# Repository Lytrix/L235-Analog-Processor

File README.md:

# L-235 Analog Processor ##

### Introduction ###
I was interested in the [SR-235](https://www.thinksrs.com/images/instr/boxcar/SR235_FPlg.jpg) as being the equivalent mathematical processor but then in Analog form which I saw in action on Hainbach's channel using this test equipment here: https://www.youtube.com/watch?v=PS_cn9-rgEs 
Also coming from a digital synthesis world using a Kurzweil K2000R Synthesizer years ago which has an awesome VAST engine with mathematical functions called FUN to combine 2 signals and apply mathematical functions on it, I still was searching for an equivalent module in eurorack but did not find any yet.

So I decided to give it a go and build a eurorack DIY version of this module to have these interesting functions available for waveform manipulation in eurorack.

I found the schematics of the SR-235 with courtesy of Stanford Research Systems:
https://www.thinksrs.com/downloads/pdfs/manuals/Boxcarm.pdf

### Main principe ###

The analog processor uses a 4 deck rotary switch to change the algorith and function. This creates different inputs paths to each IC or opamp circuitry to change the way the voltages are handled. One of the IC's is a precision multipier, the AD534. It can be bought second hand for 10 euros, but newer versions go for a whopping 200 euros. Luckily there is a cheaper version available as SMD version (AD633) which is also 10 euros. By adding an extra opamp to the Z input, you basically have the same circuit. 
The A and B inputs are full wave rectified. This is a falstad testing the out the first circuit path: [Full wave rectification test setup](https://tinyurl.com/27wkvqkx)

### Added functionalities ###

#### 1. Attenuverter with -10/+10V Offset 

Attenuverter + Offset with 2x Gain
https://therepaircafe.wordpress.com/2021/04/04/attenuverter-with-gain-and-offset/

https://tinyurl.com/2bdyzzdu
Based on 2 schematics found to build a good setup for input prepping, similar like the awesome [Olivella Modular Signos](https://www.olivellamodular.com/signos.html).

Precision Attenuverter:
https://kassu2000.blogspot.com/2018/04/precision-attenuverter-mixer.html

Added Offset:
https://modwiggler.com/forum/viewtopic.php?t=103687

#### 1b. VCA CV controlled ####
[Moritz Klein Transistor VCA example](https://www.falstad.com/circuit/circuitjs.html?ctz=CQAgjCAMB0l3BWEAmAzNALAdkggnMmAGxFYKSpKkhIao0CmAtGGAFAAu4yAHOBhnBYi-QZHAgm6YWErIE+IpGQY8RMdATIixMBj1xUyLPTBwQAEwYAzAIYBXADYdOKHnz2CV4z1AlToIjxyIh5IMGMcSB0kGC0eUKxkXnxcLCxBM3ErOycXACchEQwPYUkjPyz4NkLvEBKUDHEpZEr4ODYAJRRIPiZ1Hr7WVvFxJu4-Uc02AHdByQHkXvKR2fmWopWoNaW+irqNyC76jwEt33F6JfFYyem5sDKGx5Ew7Yeyt5fuPiO5uoadQivzYthAqFCIAGGAGAzwExYrSq8HBgTAPFYJgxqDw6SS9HQOjCPAyyDwj2iPAQWHA7SOhVQkEEDQhfAaPnaNXBTJAb1ZvNGtOqAHNwZCNvz+mJ3mK+HzIcCZTDMrx6rCxKDwMViFqxjqPK1EUL2lBYPAwLi8LigqgjIlVRzOYUdU1mg1XX5rtUHsVzDq5NtnSIA8RLlo-LbvbrweHQ-UdUcAPI0VWwlRQ6VHbouiougaC8aCqYINbfONlggyiutXbgSv0k6iH5Nx3VZ2q3yK2uOtiirvLLvp0Zc-mK5XNsZRDoM8UVfns+pTo4AD3qkj0tB064wrUEEJAAGUAJIAWQACgAZACiAB0AM4AFU6AEEAHLHg8PxOde8ANQAws+bCriwkDwhC8JMGUqBJGu6b-r+wGSJW5IoEgeDMo0h5HgA4q+z4XveR6vjsyz6CIcbkYG8wWjWZEJsaRyirwpxeO4mzDv84xxkC9ZrIyzJ8ACIJzAJAqbG8RyPIa7rmEwaj1OY4g0hEExFpoIC-gA9s4tjCgwpEeJWvGrIU44DPEGZtB0WkoPQvzcGSNzQHgYSuTiEJgWSdCmualRsEAA)

[electronic druid LM13700 example](https://electricdruid.net/wp-content/uploads/2020/04/EurorackVintageVCA-scaled.jpg)

[DIY VCA with transistors](https://sound-au.com/project213.htm)

Nice payed version: https://modulargrid.net/e/teia-mapvolt

AD633 example
https://modulargrid.net/e/seismic-industries-polarizer

LM13700 example
https://www.haraldswerk.de/VCA/Quad_VCA/Quad_VCA.html

AS3363 example

#### 2. Continuous Argument Filter X with reduced range ####
I reached out to Hainbach who was willing to share some photographs on the internals so I could look for the same brand of components.
I also incorporated his suggestion of changing the filter to a continous potentiometer and limit it to the first 3 steps (0-1M Ohms) to keep it in the audible range.

#### 3. Normalized Patch points before and after each circuit #### 
I wanted to include as many patch points as possible to have a plethora of normalised extra in/outputs on each of the different circuit blocks which are already in the SR-235. Thaty way it can be used as an ARP2600/MS-20 type of pre-routed unit and be able to use a single part of the chain if needed.

#### 4. Bi Polar Half Wave rectification ####
Beside the existing circuits already in the module like full wave rectification, a bi polar half wave option to switch to is also added.
I took inspiration of these nice utility modules where for example the CFM can be utilised to add to separate positive and negative half waves to create new waveshapes easily:
- [Mutable Kinks](https://pichenettes.github.io/mutable-instruments-documentation/modules/kinks/) Signal prep: Invert/Half Wave/Full Wave
- [BiPolar Half Wave Rectifier](http://www.cfmodular.com/BHWR)

To be able to combine new rectified waveshapes I decided to add switches for inversion and positive/negative half wave rectification so the main signal chain can easily be changed.

#### 5. CV control over the selected Argument and Function
A eurorack conversion wouldn't be complete with complete CV control over everything. Therefore I've added CV control to select different circuits via a multiplexer and using a 3-bit Flash ADC to have proper audio rate speed (hopefully!)
- [3-bit Flash ADC test](https://tinyurl.com/2b6dmdgn)

#### 6. CV control over the Argument Filter ####
The Argument Filter is upgraded to a full integrator as was used on the System 700 of Roland.
http://yusynth.net/gear/ROLAND/R700-schematics/707-INSTR-INTERF.pdf

To control the filter a Variable Resistor Ciruit is needed to change the resistance from 0-500k using a BF245 or J112:
https://www.edn.com/a-guide-to-using-fets-for-voltage-controlled-circuits-part-1
and
https://www.ednasia.com/A-guide-to-using-FETs-for-voltage-controlled-circuits--Part-2/ 

https://i.stack.imgur.com/XX1wH.png

#### 7. Additional processing types with AD633 ####

https://www.eddybergman.com/2023/06/AD633ringmodulator.html

http://seismic.industries/wp-content/uploads/2017/08/DIY_Workshop_POLARIZER_Documentation.pdf

1. Frequency Doubler (=Voltage Squarer) (Normalize output A to B to accompish this)
2. Waveshaper (=Voltage Divider A/10*B) W output to negative input opamp to Y1. Output opamp is output. 
4. Square rooter
5. Phase angle detector
6. Rectifier (already have circuits for)
7. VCA 
8. Variable Resistor
10. Ring/AM Modulator (=Multiplier) ([example1](https://musicfromouterspace.com/analogsynth_new/THE_CAVE/Ring%20Mod%20Old%20Design%20I/RingModulator.htm), [example2](https://musicfromouterspace.com/index.php?MAINTAB=SYNTHDIY&VPW=1352&VPH=697))

Great single unit with attenuators:
http://macumbista.net/?p=1314

More in depth:
https://web.archive.org/web/20070123153159/http://www.sowa.synth.net/modular/rm.html
with [schematic](https://web.archive.org/web/20070121113438/http://www.sowa.synth.net/modular/m_rm.gif)
And this example has some GREAT audio examples! Especially the divide creates really nice distortion!:
http://m.bareille.free.fr/modular1/warp633/warp633.htm

And another RM example
https://gitlab.com/rsholmes/ringer

Nice 3hp example:
https://recklessexperimentationaudio.com/products/algebra-lite

Frequency Doubling : Can be done with Waveshaper + gain.

Wavefolder/Ring Mod example:
https://note.com/solder_state/n/n9d138d74b39d

AD633 examples
https://www.youtube.com/watch?v=m6MqNZ7H99w

### Schematic overview of functions with in/outputs ###

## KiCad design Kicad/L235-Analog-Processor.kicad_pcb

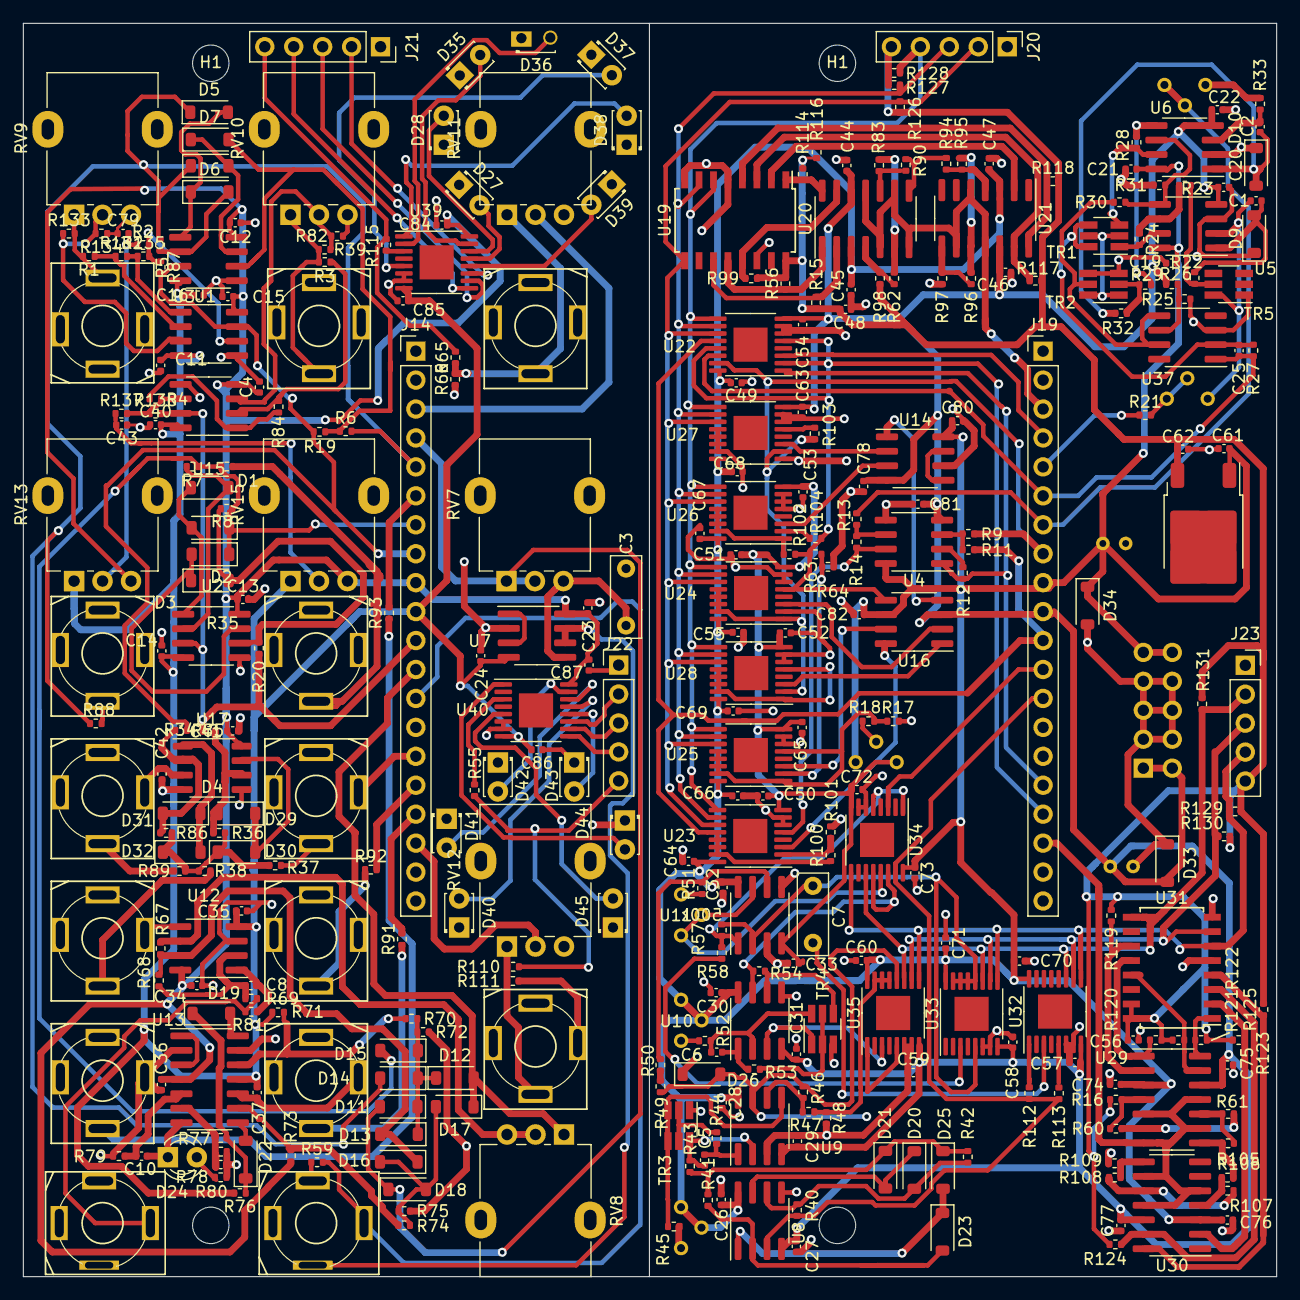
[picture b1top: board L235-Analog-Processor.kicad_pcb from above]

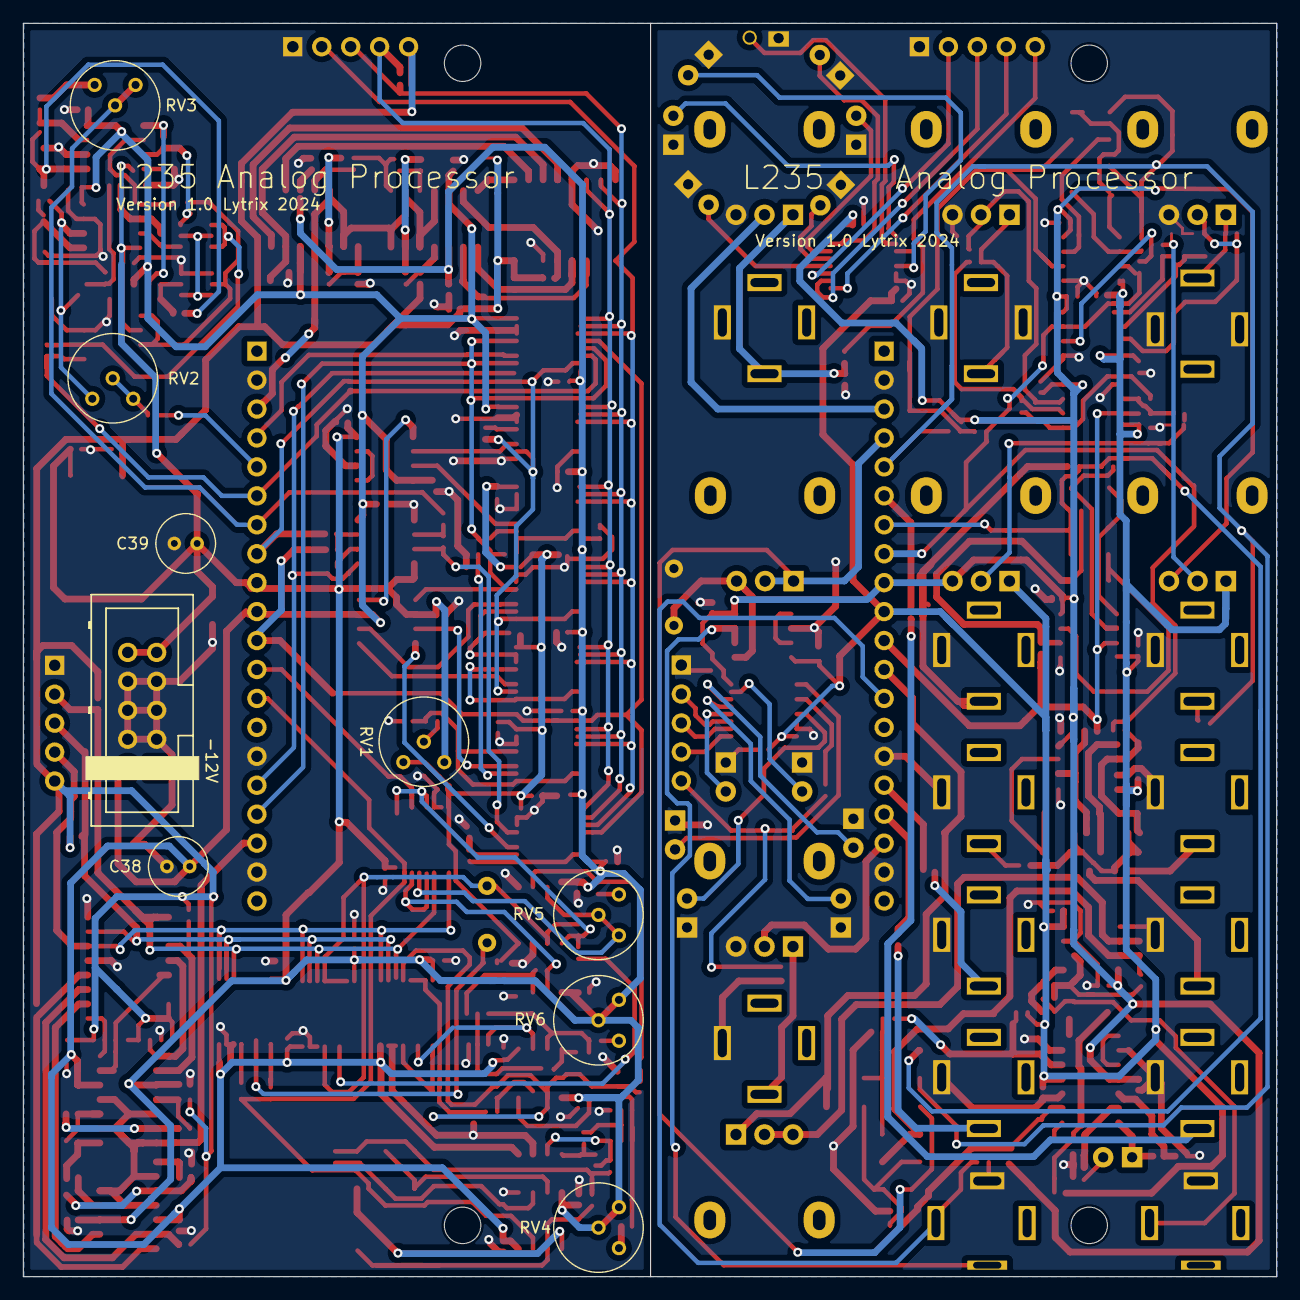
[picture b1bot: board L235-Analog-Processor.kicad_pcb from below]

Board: 2 copper layers, 110.0 x 110.0 mm, 347 parts (9 on the bottom side), 187 nets.

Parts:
C1, C2, C5, C6: 100pF; C_0402_1005Metric
C3: 0.0033uF Mylar; C_Rect_L7.0mm_W2.5mm_P5.00mm
C4, C11, C12, C13, C14, C15, C16, C19, C20, C21, C22, C23, C24, C26, C27, C28, C29, C30, C31, C32, C33, C34, C35, C36, C37, C40, C41, C42, C43, C44, C45, C46, C47, C48, C49, C50, C51, C52, C53, C54, C55, C56, C57, C58, C59, C60, C62, C63, C64, C65, C66, C67, C68, C69, C70, C71, C72, C73, C74, C75, C76, C77, C78, C79, C80, C81, C82, C84, C85, C86, C87: 100nF; C_0402_1005Metric
C7: 0.1uF; C_Rect_L7.0mm_W2.5mm_P5.00mm
C8: 100pf; C_0402_1005Metric
C9: 1nF; C_0402_1005Metric
C10: 10nF; C_0402_1005Metric
C25: 22pF; C_0402_1005Metric
C38, C39: 10uF; C_Radial_D5.0mm_H7.0mm_P2.00mm
C61: 330nF; C_0402_1005Metric
D1: U19,1; D_SOD-123
D2: U19,2; D_SOD-123
D3, D30, D32: U19,3; D_SOD-123
D4, D29, D31: U19,4; D_SOD-123
D5: U19,5; D_SOD-123
D6: U19,6; D_SOD-123
D7: U19,7; D_SOD-123
D8: U19,8; D_SOD-123
D9: U20,6; D_SOD-123
D10: U20,7; D_SOD-123
D11: U21,1; D_SOD-123
D12: U21,2; D_SOD-123
D13: U21,3; D_SOD-123
D14: U21,4; D_SOD-123
D15: U21,5; D_SOD-123
D16: U21,8; D_SOD-123
D17: U21,7; D_SOD-123
D18: U21,6; D_SOD-123
D19: U20,8; D_SOD-123
D20: U20,2; D_SOD-123
D21: U20,1; D_SOD-123
D22: D_SOD-123
D23: U20,3; D_SOD-123
D24: LED; LED_D3.0mm_Clear
D25: U20,4; D_SOD-123
D26: U20,5; D_SOD-123
D27, D28, D35, D36, D37, D38, D39, D40, D41, D42, D43, D44, D45: LED; LED_D1.8mm_W3.3mm_H2.4mm
D33, D34: 1N5819HW; D_SOD-123
H1, H1#2, H3, H3#2: MountingHole; MountingHole_3.2mm_M3_DIN965
J1: Input A; Cliff_3.5mm_Stereo_Jack
J2: Input B; Cliff_3.5mm_Stereo_Jack
J3: Function IN; Cliff_3.5mm_Stereo_Jack
J4: ( 10A / |B| ) / ( A * B / 10 ); Cliff_3.5mm_Stereo_Jack
J5: Output F(x); Cliff_3.5mm_Stereo_Jack
J6: Power; Eurorack_10_pin_header
J7: Full-Wave Rectifier B; Cliff_3.5mm_Stereo_Jack
J8: A - B; Cliff_3.5mm_Stereo_Jack
J9: Negative Half-Wave Rectifier B; Cliff_3.5mm_Stereo_Jack
J10: Half Wave A + -B; Cliff_3.5mm_Stereo_Jack
J12, J13: CV Select; Cliff_3.5mm_Stereo_Jack
J14: Conn_01x20_Pin; PinHeader_1x20_P2.54mm_Vertical
J16: Full-Wave Rectifier A; Cliff_3.5mm_Stereo_Jack
J17: Half-Wave Rectifier A; Cliff_3.5mm_Stereo_Jack
J18: √(A²+B²); Cliff_3.5mm_Stereo_Jack
J19: Conn_01x20_Socket; PinHeader_1x20_P2.54mm_Vertical
J20, J22: Conn_01x05_Socket; PinHeader_1x05_P2.54mm_Vertical
J21, J23: Conn_01x05_Pin; PinSocket_1x05_P2.54mm_Vertical
R1, R2, R3, R27, R58, R59, R77, R78, R84, R87, R112, R132, R137, R138: 100k; R_0402_1005Metric
R4, R39, R43, R54, R82, R133, R134, R135: 47k; R_0402_1005Metric
R5, R6, R7, R8, R9, R11, R12, R13, R14, R19, R20, R22, R23, R26, R29, R31, R32, R34, R36, R40, R41, R42, R44, R50, R53, R66, R67, R68, R69, R72, R75, R85, R86, R100, R102, R103, R111: 10k; R_0402_1005Metric
R15, R56, R99, R114, R116, R117, R118, R119, R120, R121, R122, R123, R124, R125, R126, R127, R128, R129, R130, R131: 4k7; R_0402_1005Metric
R16, R64, R98: 3k; R_0402_1005Metric
R17, R35, R37, R38, R55, R60, R61, R62, R80, R83, R88, R89, R90, R91, R92, R93, R94, R95, R96, R97, R105, R106, R107, R108, R109, R113, R115: 1k; R_0402_1005Metric
R18: 220k; R_0402_1005Metric
R21, R33: 75k; R_0402_1005Metric
R24, R28, R30: 20k; R_0402_1005Metric
R25: 7.1k; R_0402_1005Metric
R45, R52: 470k; R_0402_1005Metric
R46: 200; R_0402_1005Metric
R47, R48: 100; R_0402_1005Metric
R49: 10k thermistor; R_0402_1005Metric
R51: 330k; R_0402_1005Metric
R57: 10M; R_0402_1005Metric
R63: 4.3k; R_0402_1005Metric
R65, R110: 2k; R_0402_1005Metric
R70, R74: 11k; R_0402_1005Metric
R71, R73: 12k; R_0402_1005Metric
R76, R79: 1.0M; R_0402_1005Metric
R81: 220; R_0402_1005Metric
R101: 18k; R_0402_1005Metric
R104: 4.7k; R_0402_1005Metric
RV1, RV5: 100k; Potentiometer_Bourns_3339H_Vertical
RV2, RV3: 50k; Potentiometer_Bourns_3339H_Vertical
RV4, RV6: 500k; Potentiometer_Bourns_3339H_Vertical
RV7: 1M Log; Potentiometer_Alpha_RD901F-40-00D_Single_Vertical
RV8, RV9, RV10, RV13, RV15: 100k; Potentiometer_Alpha_RD901F-40-00D_Single_Vertical
RV11, RV12: 50k; Potentiometer_Alpha_RD901F-40-00D_Single_Vertical
TR1, TR2, TR3, TR4, TR5: FMBM5551; SOT-23-6_Handsoldering
U1, U2, U3, U4, U5, U6, U7, U8, U9, U10, U11, U12, U15, U37: TL082; SOIC-8_3.9x4.9mm_P1.27mm
U13: TL084; SOIC-14_3.9x8.7mm_P1.27mm
U14: RC4580; SOIC-8_3.9x4.9mm_P1.27mm
U16: AD633ARZ-RL; SOIC-8_3.9x4.9mm_P1.27mm
U17: TL082; SO-8_3.9x4.9mm_P1.27mm
U19, U31: 74HC148; SOIC-16W_5.3x10.2mm_P1.27mm
U20, U21, U29, U30: LM339; SOIC-14_3.9x8.7mm_P1.27mm
U22, U23, U24, U25, U26, U27, U28, U32, U33, U34, U35: DG408; TSSOP-16-1EP_4.4x5mm_P0.65mm_EP3x3mm
U36: LM78M05_TO252; TO-252-2
U39, U40: CD4051; TSSOP-16-1EP_4.4x5mm_P0.65mm_EP3x3mm

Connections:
(-dX/dt) or (-dX/dt*1/100): R57.1, R58.2, U11.1, U34.1 (X4), U34.5 (X5)
+5V: C48.2, C56.2, C62.2, J20.5, J21.5, J22.5, J23.5, R15.2, R16.2, R55.1, R56.2, R65.2, R98.2, R99.2, R110.2, R114.2, R115.1, R116.2, R117.2, R118.2, R119.2, R120.2, R121.2, R122.2, R123.2, R124.2, R125.2, R126.2, R127.2, R128.2, R129.2, R130.2, R131.2, U19.16 (VCC), U31.15 (E0), U31.16 (VCC), U36.3 (VO)
+12V: C4.1, C12.1, C13.1, C15.1, C19.1, C21.1, C23.1, C26.1, C28.1, C30.1, C32.1, C34.1, C36.1, C39.1, C41.1, C45.1, C47.1, C49.2, C52.2, C60.2, C61.1, C64.2, C66.2, C67.2, C68.2, C69.2, C70.2, C71.2, C73.2, C74.1, C76.1, C80.1, C82.2, C84.2, C87.2, D34.1 (K), J6.9, J6.10, J14.9, J19.9, R73.1, RV1.1, RV4.1, RV4.2, RV6.1, RV6.2, RV13.3, RV15.3, U1.8 (V+), U2.8 (V+), U3.8 (V+), U4.8 (V+), U5.8 (V+), U6.8 (V+), U7.8 (V+), U8.8 (V+), U9.8 (V+), U10.8 (V+), U11.8 (V+), U12.8 (V+), U13.4 (V+), U14.8 (V+), U15.4 (V-), U16.6 (+VS), U17.8 (V+), U20.3 (V+), U21.3 (V+), U22.16 (VDD), U23.16 (VDD), U24.16 (VDD), U25.16 (VDD), U26.16 (VDD), U27.16 (VDD), U28.16 (VDD), U29.3 (V+), U30.3 (V+), U32.16 (VDD), U33.16 (VDD), U34.16 (VDD), U35.16 (VDD), U36.1 (VI), U39.16 (VDD), U40.16 (VDD)
-12V: C11.2, C14.2, C16.2, C20.2, C22.2, C24.2, C27.2, C29.2, C31.2, C33.2, C35.2, C37.2, C38.2, C40.2, C42.2, C44.2, C46.2, C50.2, C51.2, C53.2, C54.2, C55.2, C57.2, C58.2, C59.2, C63.2, C65.2, C72.2, C75.2, C77.2, C78.2, C81.2, C85.2, C86.2, D33.2 (A), J6.1, J6.2, J14.10, J19.10, R26.1, R71.2, R76.2, RV1.3, RV13.1, RV15.1, U1.4 (V-), U2.4 (V-), U3.4 (V-), U4.4 (V-), U5.4 (V-), U6.4 (V-), U7.4 (V-), U8.4 (V-), U9.4 (V-), U10.4 (V-), U11.4 (V-), U12.4 (V-), U13.11 (V-), U14.4 (V-), U15.8 (V+), U16.3 (-VS), U17.4 (V-), U20.12 (V-), U21.12 (V-), U22.8 (VSS), U23.8 (VSS), U24.8 (VSS), U25.8 (VSS), U26.8 (VSS), U27.8 (VSS), U28.8 (VSS), U29.12 (V-), U30.12 (V-), U32.8 (VSS), U33.8 (VSS), U34.8 (VSS), U35.8 (VSS), U39.8 (VSS), U40.8 (VSS)
-Output: D13.2 (A), D16.1 (K), R67.1, R68.2, U12.7
-|B|: R14.2, U4.7, U23.5 (X5)
<X>: J3.T, J14.13, J19.13, R40.1, R59.2, R112.1, R113.1, U8.3 (+), U34.15 (X2)
A: J14.8, J19.8, R9.1, R19.1, R85.1, R87.2, R103.1, U1.7, U3.3 (+), U22.15 (X2), U24.1 (X4), U24.12 (X3), U24.13 (X0), U24.14 (X1), U24.15 (X2), U27.2 (X6), U28.2 (X6)
A0: J20.2, J21.2, R126.1, U19.9 (A0), U22.11 (A), U23.11 (A), U24.11 (A), U25.11 (A), U26.11 (A), U27.11 (A), U28.11 (A), U39.11 (A)
A1: J20.3, J21.3, R127.1, U19.7 (A1), U22.10 (B), U23.10 (B), U24.10 (B), U25.10 (B), U26.10 (B), U27.10 (B), U28.10 (B), U39.10 (B)
A2: J20.4, J21.4, R128.1, U19.6 (A2), U22.9 (C), U23.9 (C), U24.9 (C), U25.9 (C), U26.9 (C), U27.9 (C), U28.9 (C), U39.9 (C)
A - B: J14.16, J19.16, R12.2, R92.2, U4.1, U22.1 (X4)
AD534_OUT: J14.17, J19.17, R63.2, R91.2, R102.1, R104.1, U16.5 (W), U22.2 (X6), U22.5 (X5), U22.13 (X0), U24.5 (X5)
AD534_X1: U16.7 (X1), U25.3 (X)
AD534_X2: U16.8 (X2), U23.3 (X)
AD534_Y1: U16.1 (Y1), U28.3 (X)
AD534_Y2: U16.2 (Y2), U24.3 (X)
AD534_Z1: U14.3 (+), U26.3 (X)
AD534_Z2: U14.2 (-), U27.3 (X)
B: J14.11, J19.11, R11.1, R20.1, R34.1, R100.1, R138.2, U2.3 (+), U15.7, U22.12 (X3), U23.1 (X4), U23.12 (X3), U23.13 (X0), U23.14 (X1), U23.15 (X2)
B0: J22.2, J23.2, R131.1, U31.9 (A0), U32.11 (A), U33.11 (A), U34.11 (A), U35.11 (A), U40.11 (A)
B1: J22.3, J23.3, R130.1, U31.7 (A1), U32.10 (B), U33.10 (B), U34.10 (B), U35.10 (B), U40.10 (B)
B2: J22.4, J23.4, R129.1, U31.6 (A2), U32.9 (C), U33.9 (C), U34.9 (C), U35.9 (C), U40.9 (C)
B|: D30.1 (K), D32.1 (K), R36.2, R37.1, R38.1, R86.2, R89.1
CA3046_B3: TR4.1, U10.3 (+), U35.3 (X)
CV_FUNCTION: J14.18, J19.18, RV12.2, U29.5 (+), U29.7 (+), U29.9 (+), U29.11 (+), U30.5 (+), U30.9 (+), U30.11 (+)
CV_SELECT: J14.3, J19.3, RV11.2, U20.5 (+), U20.7 (+), U20.9 (+), U20.11 (+), U21.5 (+), U21.9 (+), U21.11 (+)
F1: C7.2, R57.2, U11.2 (-), U33.5 (X5), U33.12 (X3), U33.13 (X0), U33.14 (X1), U33.15 (X2)
F1-1/100: C7.1, U32.3 (X)
F2: R58.1, U33.3 (X)
Function Out: D12.2 (A), D17.1 (K), J14.12, J19.12, RV8.1, U34.3 (X)
GND: C3.2, C4.2, C9.2, C11.1, C12.2, C13.2, C14.1, C15.2, C16.1, C19.2, C20.1, C21.2, C22.1, C23.2, C24.1, C26.2, C27.1, C28.2, C29.1, C30.2, C31.1, C32.2, C33.1, C34.2, C35.1, C36.2, C37.1, C38.1, C39.2, C40.1, C41.2, C42.1, C43.1, C44.1, C45.2, C46.1, C47.2, C48.1, C49.1, C50.1, C51.1, C52.1, C53.1, C54.1, C55.1, C56.1, C57.1, C58.1, C59.1, C60.1, C61.2, C62.1, C63.1, C64.1, C65.1, C66.1, C67.1, C68.1, C69.1, C70.1, C71.1, C72.1, C73.1, C74.2, C75.1, C76.2, C77.1, C78.1, C79.1, C80.2, C81.1, C82.1, C84.1, C85.1, C86.1, C87.1, D9.1 (K), D10.1 (K), D26.1 (K), D27.1 (K), D28.1 (K), D33.1 (K), D34.2 (A), D35.1 (K), D36.1 (K), D37.1 (K), D38.1 (K), D39.1 (K), D40.1 (K), D41.1 (K), D42.1 (K), D43.1 (K), D44.1 (K), D45.1 (K), J1.G, J1.TN, J2.G, J2.TN, J3.G, J4.G, J5.G, J6.3, J6.4, J6.5, J6.6, J6.7, J6.8, J7.G, J8.G, J9.G, J10.G, J12.G, J13.G, J14.2, J14.15, J14.19, J16.G, J17.G, J18.G, J19.2, J19.15, J19.19, J20.1, J21.1, J22.1, J23.1, R17.1, R25.2, R31.1, R48.2, R59.1, R64.1, R66.1, R72.1, R75.1, R78.2, R79.2, R80.1, R82.1, R97.1, R101.2, R109.1, R111.1, R134.1, RV9.3, RV10.3, RV11.3, RV12.3, TR2.3, TR2.4, TR3.1, TR4.3, TR5.1, U1.5 (+), U2.5 (+), U3.5 (+), U4.5 (+), U5.3 (+), U6.2 (-), U7.2 (-), U8.5 (+), U9.3 (+), U10.5 (+), U11.3 (+), U11.5 (+), U12.3 (+), U12.5 (+), U13.2 (-), U13.10 (+), U13.13 (-), U14.6 (-), U15.5 (+), U17.3 (+), U17.5 (+), U19.5 (EI), U19.8 (GND), U19.14 (GS), U22.6 (Inh), U22.7 (VEE), U23.6 (Inh), U23.7 (VEE), U24.2 (X6), U24.6 (Inh), U24.7 (VEE), U25.6 (Inh), U25.7 (VEE), U26.5 (X5), U26.6 (Inh), U26.7 (VEE), U27.1 (X4), U27.6 (Inh), U27.7 (VEE), U27.12 (X3), U27.13 (X0), U27.14 (X1), U27.15 (X2), U28.6 (Inh), U28.7 (VEE), U31.5 (EI), U31.8 (GND), U32.6 (Inh), U32.7 (VEE), U33.6 (Inh), U33.7 (VEE), U34.6 (Inh), U34.7 (VEE), U35.6 (Inh), U35.7 (VEE), U36.2 (GND), U37.3 (+), U39.6 (Inh), U39.7 (VEE), U40.6 (Inh), U40.7 (VEE)
LED_A1: D27.2 (A), U39.13 (X0)
LED_A2: D28.2 (A), U39.14 (X1)
LED_A3: D35.2 (A), U39.15 (X2)
LED_A4: D39.2 (A), U39.12 (X3)
LED_A5: D38.2 (A), U39.1 (X4)
LED_A6: D37.2 (A), U39.5 (X5)
LED_A7: D36.2 (A), U39.2 (X6)
LED_B1: D40.2 (A), U40.13 (X0)
LED_B2: D41.2 (A), U40.14 (X1)
LED_B3: D42.2 (A), U40.15 (X2)
LED_B4: D43.2 (A), U40.12 (X3)
LED_B5: D44.2 (A), U40.1 (X4)
LED_B6: D45.2 (A), U40.5 (X5)
unnamed: C5.2, R44.1, U9.1
unnamed: C6.2, R53.1, U10.1
unnamed: C8.2, R81.2, U12.1
unnamed: C43.2, R137.1, RV15.2
unnamed: C79.2, R2.1, RV13.2
unnamed: D1.2 (A), R7.1, U2.2 (-)
unnamed: D1.1 (K), D2.2 (A), U2.1
unnamed: D3.2 (A), D4.1 (K), U2.7
unnamed: D4.2 (A), R8.1, R20.2, U2.6 (-)
unnamed: D5.2 (A), D6.1 (K), U3.1
unnamed: D6.2 (A), R5.1, U3.2 (-)
unnamed: D7.2 (A), R6.1, R19.2, U3.6 (-)
unnamed: D7.1 (K), D8.2 (A), U3.7
unnamed: C1.2, D9.2 (A), R22.1, U5.1
unnamed: C2.1, D10.2 (A), R32.1, U6.1
unnamed: D11.1 (K), D12.1 (K), D13.1 (K), D14.1 (K), D15.1 (K), R70.2, R72.2
unnamed: D16.2 (A), D17.2 (A), D18.2 (A), R74.2, R75.2
unnamed: D19.2 (A), U13.14
unnamed: D19.1 (K), D22.1 (K), R76.1, R77.2
unnamed: D20.2 (A), R40.2, R42.1, U8.6 (-)
unnamed: D20.1 (K), D21.2 (A), U8.7
unnamed: D21.1 (K), D25.1 (K), R41.2, R42.2, R43.1
unnamed: D22.2 (A), U13.8
unnamed: D23.2 (A), R41.1, U8.2 (-)
unnamed: D23.1 (K), D25.2 (A), U8.1
unnamed: D24.2 (A), R80.2
unnamed: C10.2, D24.1 (K), U13.7
unnamed: D29.2 (A), R34.2, R36.1, U17.6 (-)
unnamed: D29.1 (K), D30.2 (A), U17.7
unnamed: D31.2 (A), R85.2, R86.1, U17.2 (-)
unnamed: D31.1 (K), D32.2 (A), U17.1
unnamed: J1.T, R1.2, R133.2, RV9.1
unnamed: J2.T, R3.1, R39.2, RV10.1
unnamed: J4.T, R91.1
unnamed: J5.T, R69.1, R81.1
unnamed: J7.T, R35.2
unnamed: J8.T, R92.1
unnamed: J9.T, R37.2
unnamed: J10.T, R38.2
unnamed: J12.T, R65.1, R66.2, RV11.1
unnamed: J13.T, R110.1, R111.2, RV12.1
unnamed: J16.T, R88.2
unnamed: J17.T, R89.2
unnamed: J18.T, R93.1
unnamed: R4.1, R84.2, U15.1
unnamed: R18.2, RV1.2
unnamed: R21.2, RV2.1, RV2.2
unnamed: R22.2, R23.1, TR5.5
unnamed: R24.2, TR1.1, U5.7
unnamed: R28.1, TR1.3, U6.7
unnamed: R29.2, R32.2, TR2.2
unnamed: R33.2, RV3.1
unnamed: R44.2, TR3.2, TR3.5
unnamed: R45.2, RV4.3
unnamed: R49.1, R50.2
unnamed: R51.1, RV5.1
unnamed: R52.2, RV6.3
unnamed: R53.2, TR4.2, TR4.5
unnamed: R132.2, R135.1, U1.1
unnamed: TR1.2, TR1.5, TR2.1, TR2.6
unnamed: R133.1, R134.2, RV9.2, U1.3 (+)
unnamed: R1.1, R132.1, U1.2 (-)
unnamed: R2.2, R87.1, R135.2, U1.6 (-)
unnamed: R9.2, R11.2, U4.3 (+)
unnamed: R12.1, U4.2 (-)
unnamed: R13.2, R14.1, U4.6 (-)
unnamed: C1.1, RV2.3, TR5.6, U5.2 (-)
unnamed: R30.2, R31.2, U5.5 (+), U6.6 (-)
unnamed: R23.2, R24.1, U5.6 (-)
unnamed: C2.2, R33.1, U6.3 (+)
unnamed: R28.2, R29.1, U6.5 (+)
unnamed: U7.1, U7.3 (+)
unnamed: C3.1, RV7.3, U7.5 (+)
unnamed: J3.TN, U7.6 (-), U7.7
unnamed: C5.1, R43.2, TR3.6, U9.2 (-)
unnamed: R45.1, TR3.3, TR3.4, U9.5 (+)
unnamed: R46.2, R47.1, U9.6 (-)
unnamed: C6.1, R52.1, TR4.6, U10.2 (-)
unnamed: R54.2, TR4.4, U10.6 (-)
unnamed: R50.1, R51.2, U11.6 (-)
unnamed: C8.1, R68.1, R69.2, U12.2 (-)
unnamed: R67.2, RV8.2, RV8.3, U12.6 (-)
unnamed: U13.1, U13.3 (+)
unnamed: C10.1, R79.1, U13.5 (+)
unnamed: C9.1, R77.1, R78.1, U13.6 (-)
unnamed: R73.2, R74.1, U13.9 (-)
unnamed: R70.1, R71.1, U13.12 (+)
unnamed: U14.5 (+), U14.7
unnamed: R39.1, R82.2, RV10.2, U15.3 (+)
unnamed: R3.2, R84.1, U15.2 (-)
unnamed: R4.2, R137.2, R138.1, U15.6 (-)
unnamed: U14.1, U16.4 (Z)
unnamed: R15.1, U19.11 (1), U20.2
unnamed: R56.1, U19.12 (2), U20.1
unnamed: R99.1, U19.13 (3), U20.13
unnamed: R114.1, U19.1 (4), U20.14
unnamed: R116.1, U19.2 (5), U21.2
unnamed: R117.1, U19.3 (6), U21.13
unnamed: R118.1, U19.4 (7), U21.14
unnamed: R62.2, R98.1, U20.4 (-)
unnamed: R62.1, R83.2, U20.6 (-)
unnamed: R83.1, R90.2, U20.10 (-)
unnamed: R90.1, R94.2, U20.8 (-)
unnamed: R94.1, R95.2, U21.4 (-)
unnamed: R95.1, R96.2, U21.10 (-)
unnamed: R96.1, R97.2, U21.8 (-)
unnamed: R100.2, R101.1, U23.2 (X6)
unnamed: R102.2, U26.1 (X4), U26.12 (X3), U26.13 (X0), U26.14 (X1), U26.15 (X2)
unnamed: R104.2, U26.2 (X6)
unnamed: R103.2, U27.5 (X5)
unnamed: R16.1, R60.2, U29.4 (-)
unnamed: R60.1, R61.2, U29.6 (-)
unnamed: R61.1, R105.2, U29.10 (-)
unnamed: R105.1, R106.2, U29.8 (-)
unnamed: R106.1, R107.2, U30.4 (-)
unnamed: R107.1, R108.2, U30.10 (-)
unnamed: R108.1, R109.2, U30.8 (-)
unnamed: R119.1, U29.2, U31.11 (1)
unnamed: R120.1, U29.1, U31.12 (2)
unnamed: R121.1, U29.13, U31.13 (3)
unnamed: R122.1, U29.14, U31.1 (4)
unnamed: R123.1, U30.2, U31.2 (5)
unnamed: R124.1, U30.13, U31.3 (6)
unnamed: R125.1, U30.14, U31.4 (7)
unnamed: R112.2, U32.1 (X4)
unnamed: R113.2, U32.5 (X5)
unnamed: C25.1, R27.1, TR1.4, TR1.6, U37.2 (-)
unnamed: R30.1, TR2.5, U37.5 (+), U37.7
unnamed: R25.1, R26.2, U37.6 (-)
unnamed: R115.2, U39.3 (X)
unnamed: R55.2, U40.3 (X)
Sine: R63.1, R64.2, U25.2 (X6)
Volt_ref_X: R17.2, R18.1, U25.1 (X4), U25.5 (X5), U25.12 (X3), U25.13 (X0), U25.14 (X1), U25.15 (X2)
Volt_ref_Y: U28.1 (X4), U28.5 (X5), U28.12 (X3), U28.13 (X0), U28.14 (X1), U28.15 (X2)
X: D11.2 (A), D18.1 (K), J14.4, J19.4, RV7.1, RV7.2, U22.3 (X)
X²: D26.2 (A), R46.1, R49.2, U9.7, U35.1 (X4), U35.5 (X5), U35.12 (X3)
ln |x|: RV5.2, RV5.3, U11.7, U34.13 (X0)
|A|: D5.1 (K), D8.1 (K), D14.2 (A), J14.5, J19.5, R5.2, R6.2, R21.1, R88.1
|B|: D2.1 (K), D3.1 (K), D15.2 (A), J14.7, J19.7, R7.2, R8.2, R13.1, R35.1, RV3.2, RV3.3
√(A²+B²): C25.2, J14.6, J19.6, R27.2, R93.2, U22.14 (X1), U37.1
√|x|: R47.2, R48.1, U35.13 (X0), U35.14 (X1), U35.15 (X2)
√|x| or X²: R54.1, U10.7, U34.12 (X3), U34.14 (X1)

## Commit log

2024-02-14 Reduced file size
2024-02-14 Moved Kicad files to kicad folder
2024-02-14 fixed numbering order
2024-02-14 Fixed symbol pins AD534JH, Added IC power Rectifier/Inverse
2024-02-14 fixed double U14 annotation
2024-02-14 fixed double U16 annotation
2024-04-04 Changed parts to smd and added CV selector
2024-04-04 Added example of 3-bit flash adc and explained choice AD633
2024-04-05 Added header and mounting points
2024-04-10 Optimized PCB routing, started with variable resistor
2024-04-11 All components routed
2024-04-11 Fixed missing routing voltage/gnd
2024-04-12 Added Frontpanel
2024-04-12 Added picture of SRS-235
2024-04-12 changed diode footprints to SOT-123
2024-04-15 Added test run
2024-04-17 Added leds selectors
2024-04-17 Fixed frontpanel and moved overload led
2024-04-18 Added missing Vlogic to comparators
2024-04-18 Flipped +- comparators to fix H/L order to actually work with logic table
2024-04-18 Cleanup trace thickness, text alignment
2024-04-19 Removed invert jacks for attenuverter + offset knob
2024-04-23 Replaced 4051 with DG408 to allow negative -10V voltages
2024-04-23 Updated frontpanel with Bias knobs, removing invert outs
2024-05-05 Fixed attenuverter circuit after breadboard testing
